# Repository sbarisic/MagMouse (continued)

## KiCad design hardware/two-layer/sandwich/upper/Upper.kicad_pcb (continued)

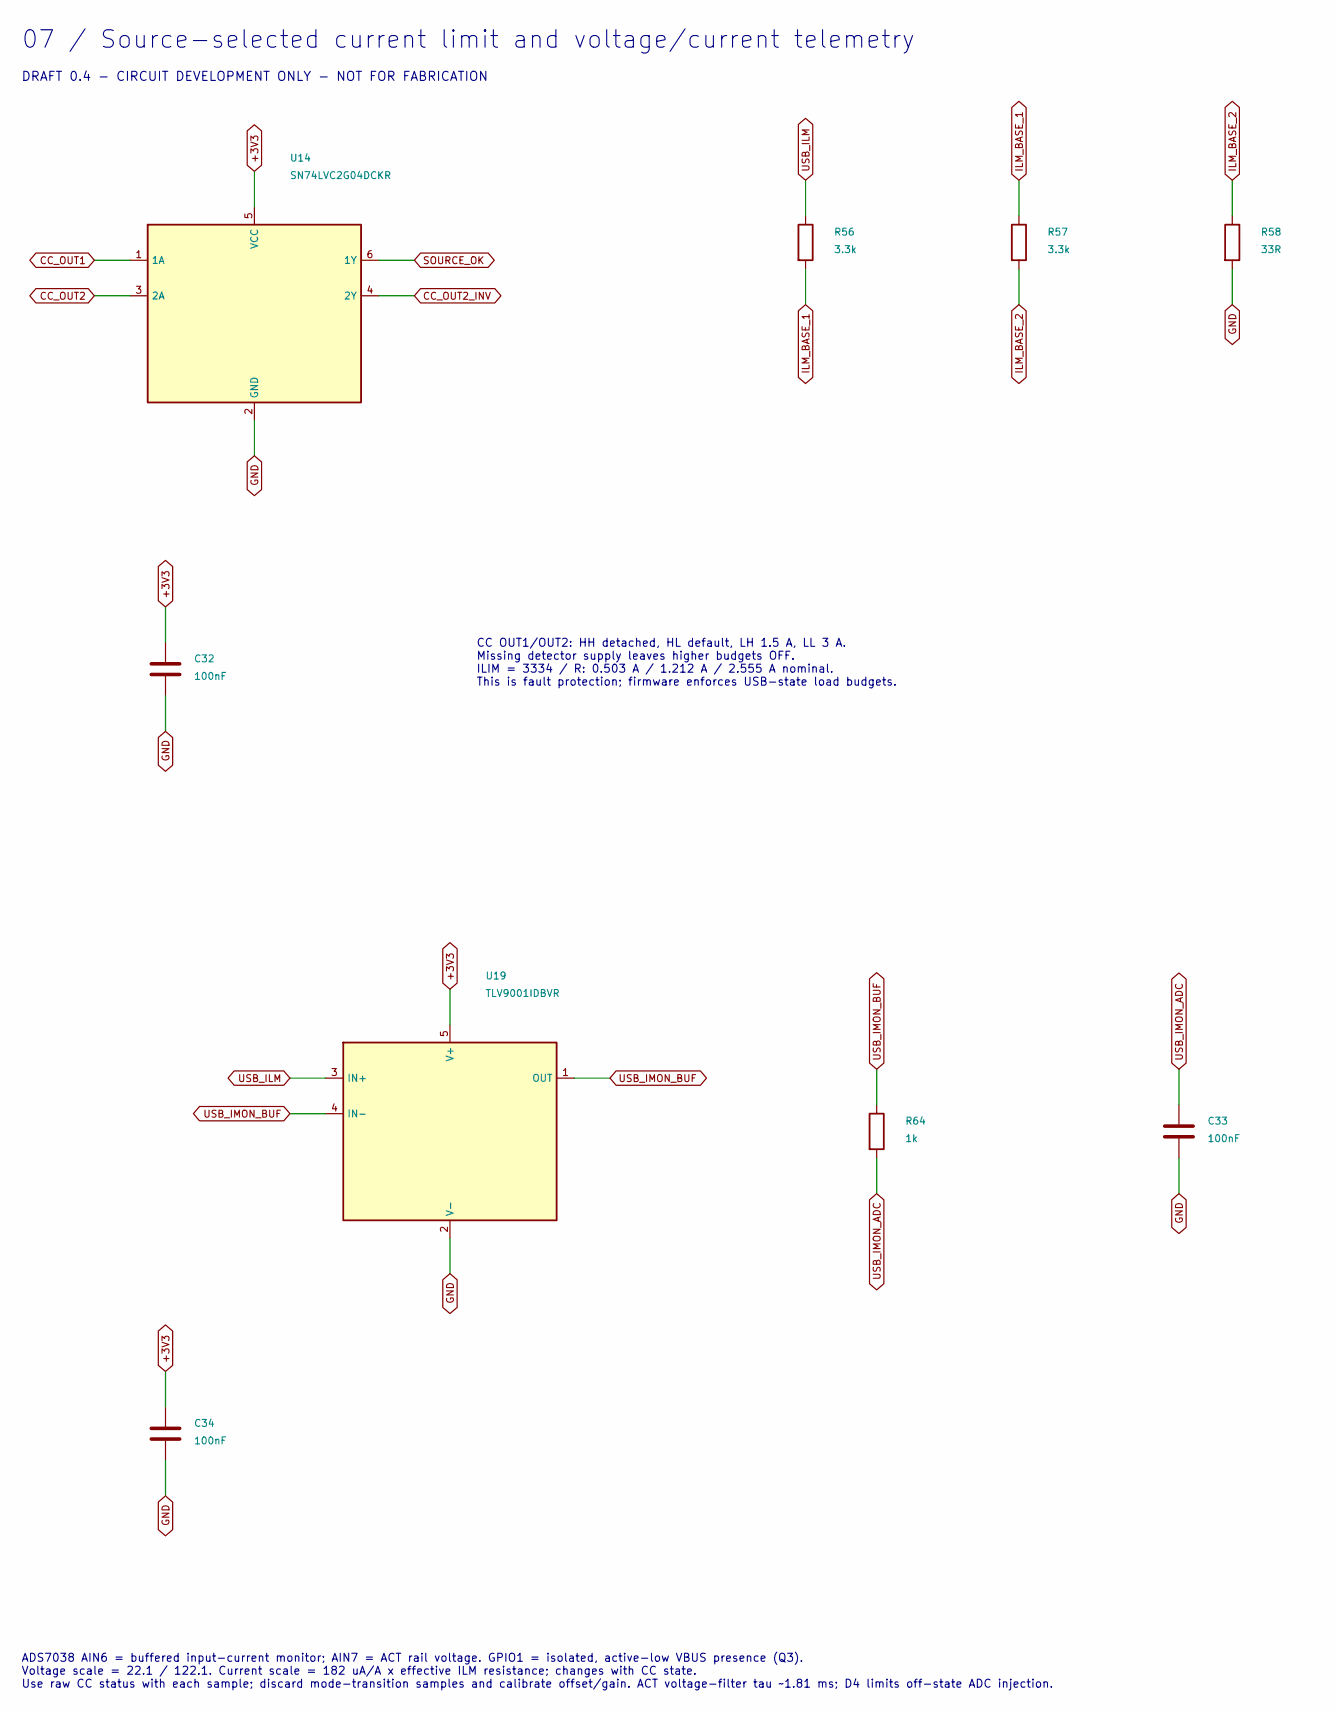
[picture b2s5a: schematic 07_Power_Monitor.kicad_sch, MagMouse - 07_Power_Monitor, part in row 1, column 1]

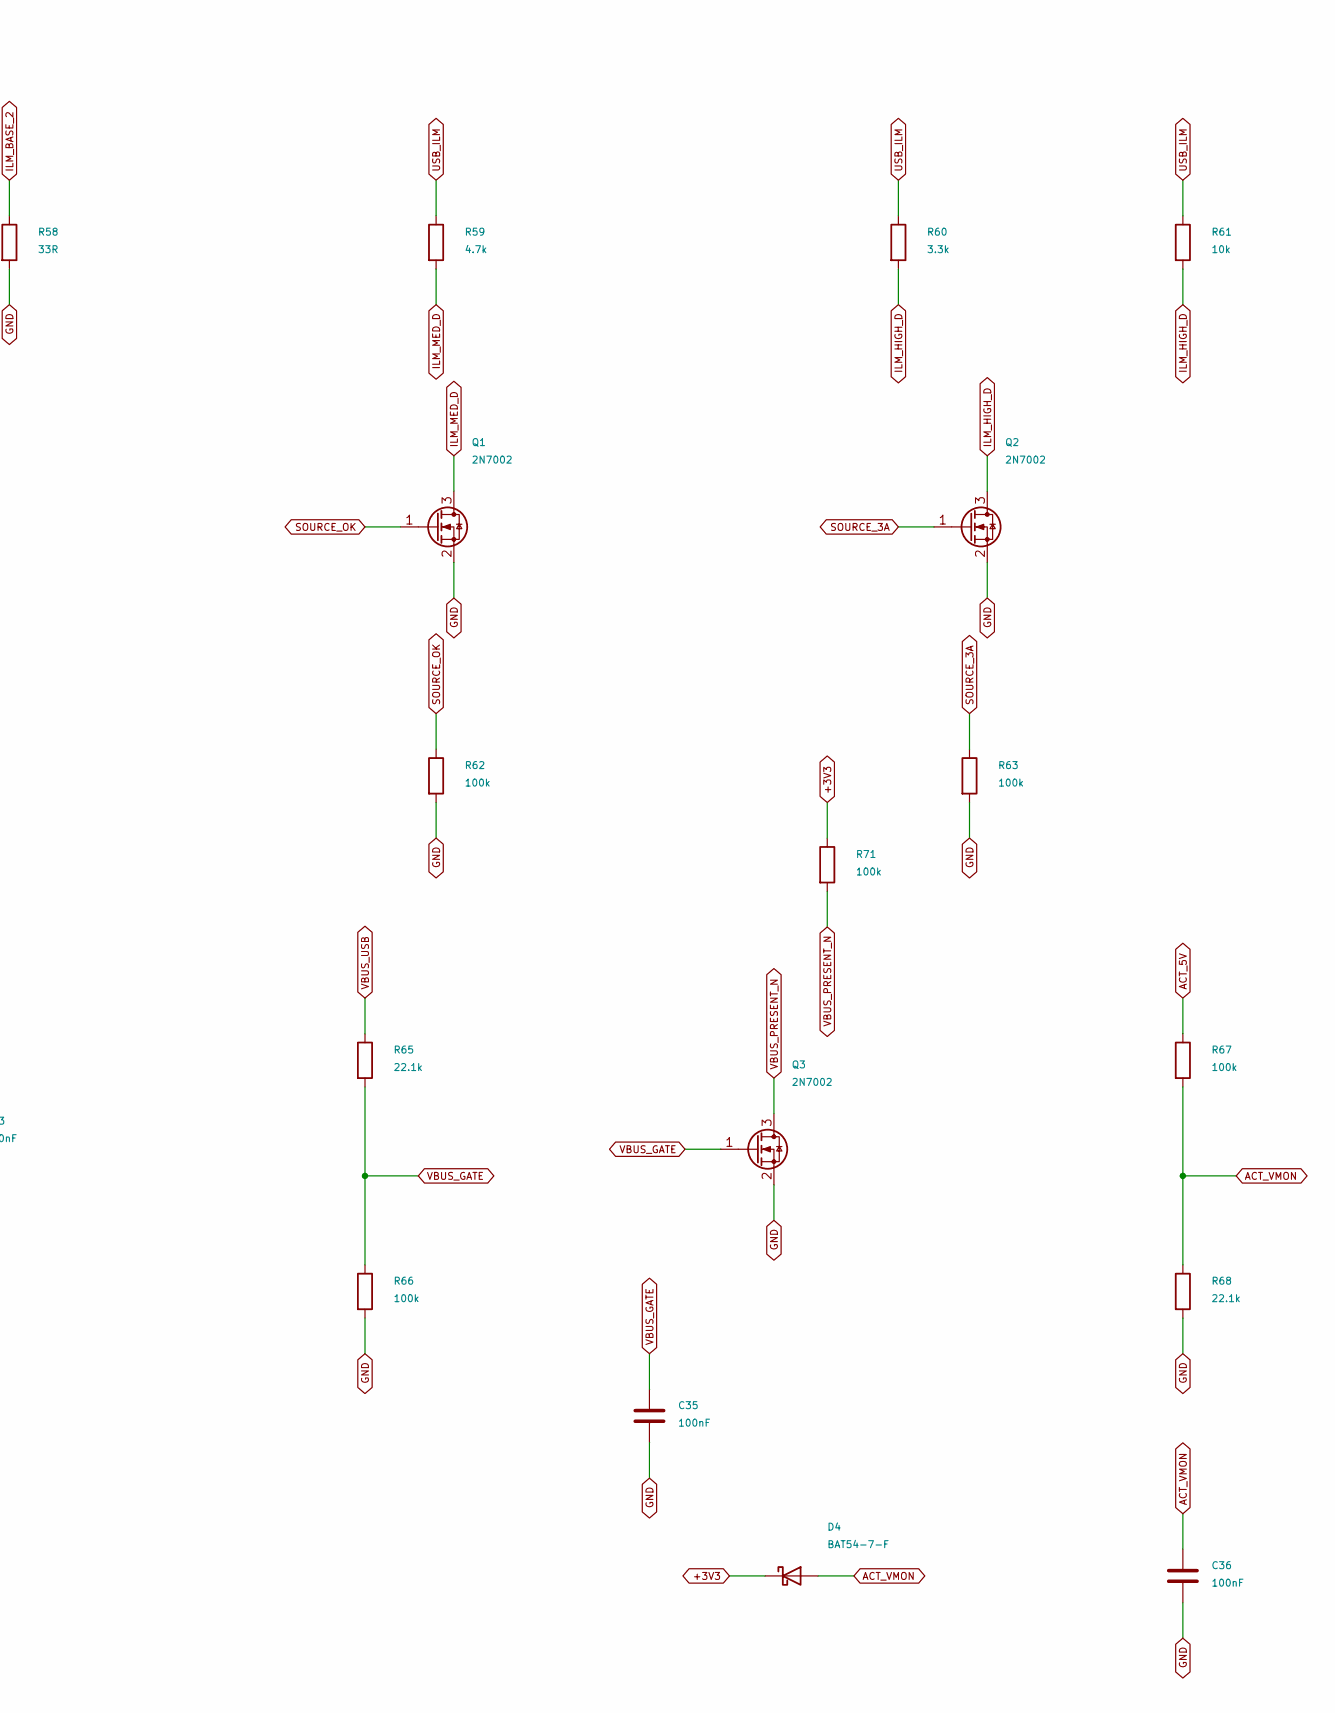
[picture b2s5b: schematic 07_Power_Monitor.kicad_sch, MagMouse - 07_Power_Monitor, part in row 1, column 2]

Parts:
C32, C33, C34, C35, C36: 100nF; C_1206_3216Metric; Rating 50 V, X7R, 10%; MPN CC1206KRX7R9BB104
D4: BAT54-7-F; SOT-23; MPN BAT54-7-F; LCSC C106920
Q1, Q2, Q3: 2N7002; SOT-23; MPN 2N7002; LCSC C8545
R56, R57, R60: 3.3k; R_1206_3216Metric; Rating 0.25 W, 1%; MPN RC1206FR-073K3L
R58: 33R; R_1206_3216Metric; Rating 0.25 W, 1%; MPN RC1206FR-0733RL
R59: 4.7k; R_1206_3216Metric; Rating 0.25 W, 1%; MPN RC1206FR-074K7L
R61: 10k; R_1206_3216Metric; Rating 0.25 W, 1%; MPN RC1206FR-0710KL
R62, R63, R66, R67, R71: 100k; R_1206_3216Metric; Rating 0.25 W, 1%; MPN RC1206FR-07100KL
R64: 1k; R_1206_3216Metric; Rating 0.25 W, 1%; MPN RC1206FR-071KL
R65, R68: 22.1k; R_1206_3216Metric; Rating 0.25 W, 1%; MPN RC1206FR-0722K1L
U14: SN74LVC2G04DCKR; SOT-363_SC-70-6; MPN SN74LVC2G04DCKR; LCSC C105251
U19: TLV9001IDBVR; SOT-23-5; MPN TLV9001IDBVR; LCSC C398363

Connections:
+3V3: C32.1, C34.1, D4.3 (K), R71.1, U14.5 (VCC), U19.5 (V+); also elsewhere on the board
ACT_5V: R67.1; also elsewhere on the board
ACT_VMON: C36.1, D4.1 (A), R67.2, R68.1; also elsewhere on the board
CC_OUT1: U14.1 (1A); also elsewhere on the board
CC_OUT2: U14.3 (2A); also elsewhere on the board
CC_OUT2_INV: U14.4 (2Y); also elsewhere on the board
GND: C32.2, C33.2, C34.2, C35.2, C36.2, Q1.2 (S), Q2.2 (S), Q3.2 (S), R58.2, R62.2, R63.2, R66.2, R68.2, U14.2 (GND), U19.2 (V-); also elsewhere on the board
ILM_BASE_1: R56.2, R57.1
ILM_BASE_2: R57.2, R58.1
ILM_HIGH_D: Q2.3 (D), R60.2, R61.2
ILM_MED_D: Q1.3 (D), R59.2
SOURCE_3A: Q2.1 (G), R63.1; also elsewhere on the board
SOURCE_OK: Q1.1 (G), R62.1, U14.6 (1Y); also elsewhere on the board
USB_ILM: R56.1, R59.1, R60.1, R61.1, U19.3 (IN+); also elsewhere on the board
USB_IMON_ADC: C33.1, R64.2; also elsewhere on the board
USB_IMON_BUF: R64.1, U19.1 (OUT), U19.4 (IN-)
VBUS_GATE: C35.1, Q3.1 (G), R65.2, R66.1
VBUS_PRESENT_N: Q3.3 (D), R71.2; also elsewhere on the board
VBUS_USB: R65.1; also elsewhere on the board

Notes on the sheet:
07 / Source-selected current limit and voltage/current telemetry
DRAFT 0.4 - CIRCUIT DEVELOPMENT ONLY - NOT FOR FABRICATION
CC OUT1/OUT2: HH detached, HL default, LH 1.5 A, LL 3 A. Missing detector supply leaves higher budgets OFF. ILIM = 3334 / R: 0.503 A / 1.212 A / 2.555 A nominal. This is fault protection; firmware enforces USB-state load budgets.
ADS7038 AIN6 = buffered input-current monitor; AIN7 = ACT rail voltage. GPIO1 = isolated, active-low VBUS presence (Q3). Voltage scale = 22.1 / 122.1. Current scale = 182 uA/A x effective ILM resistance; changes with CC state. Use raw CC status with each sample; discard mode-transition samples and 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

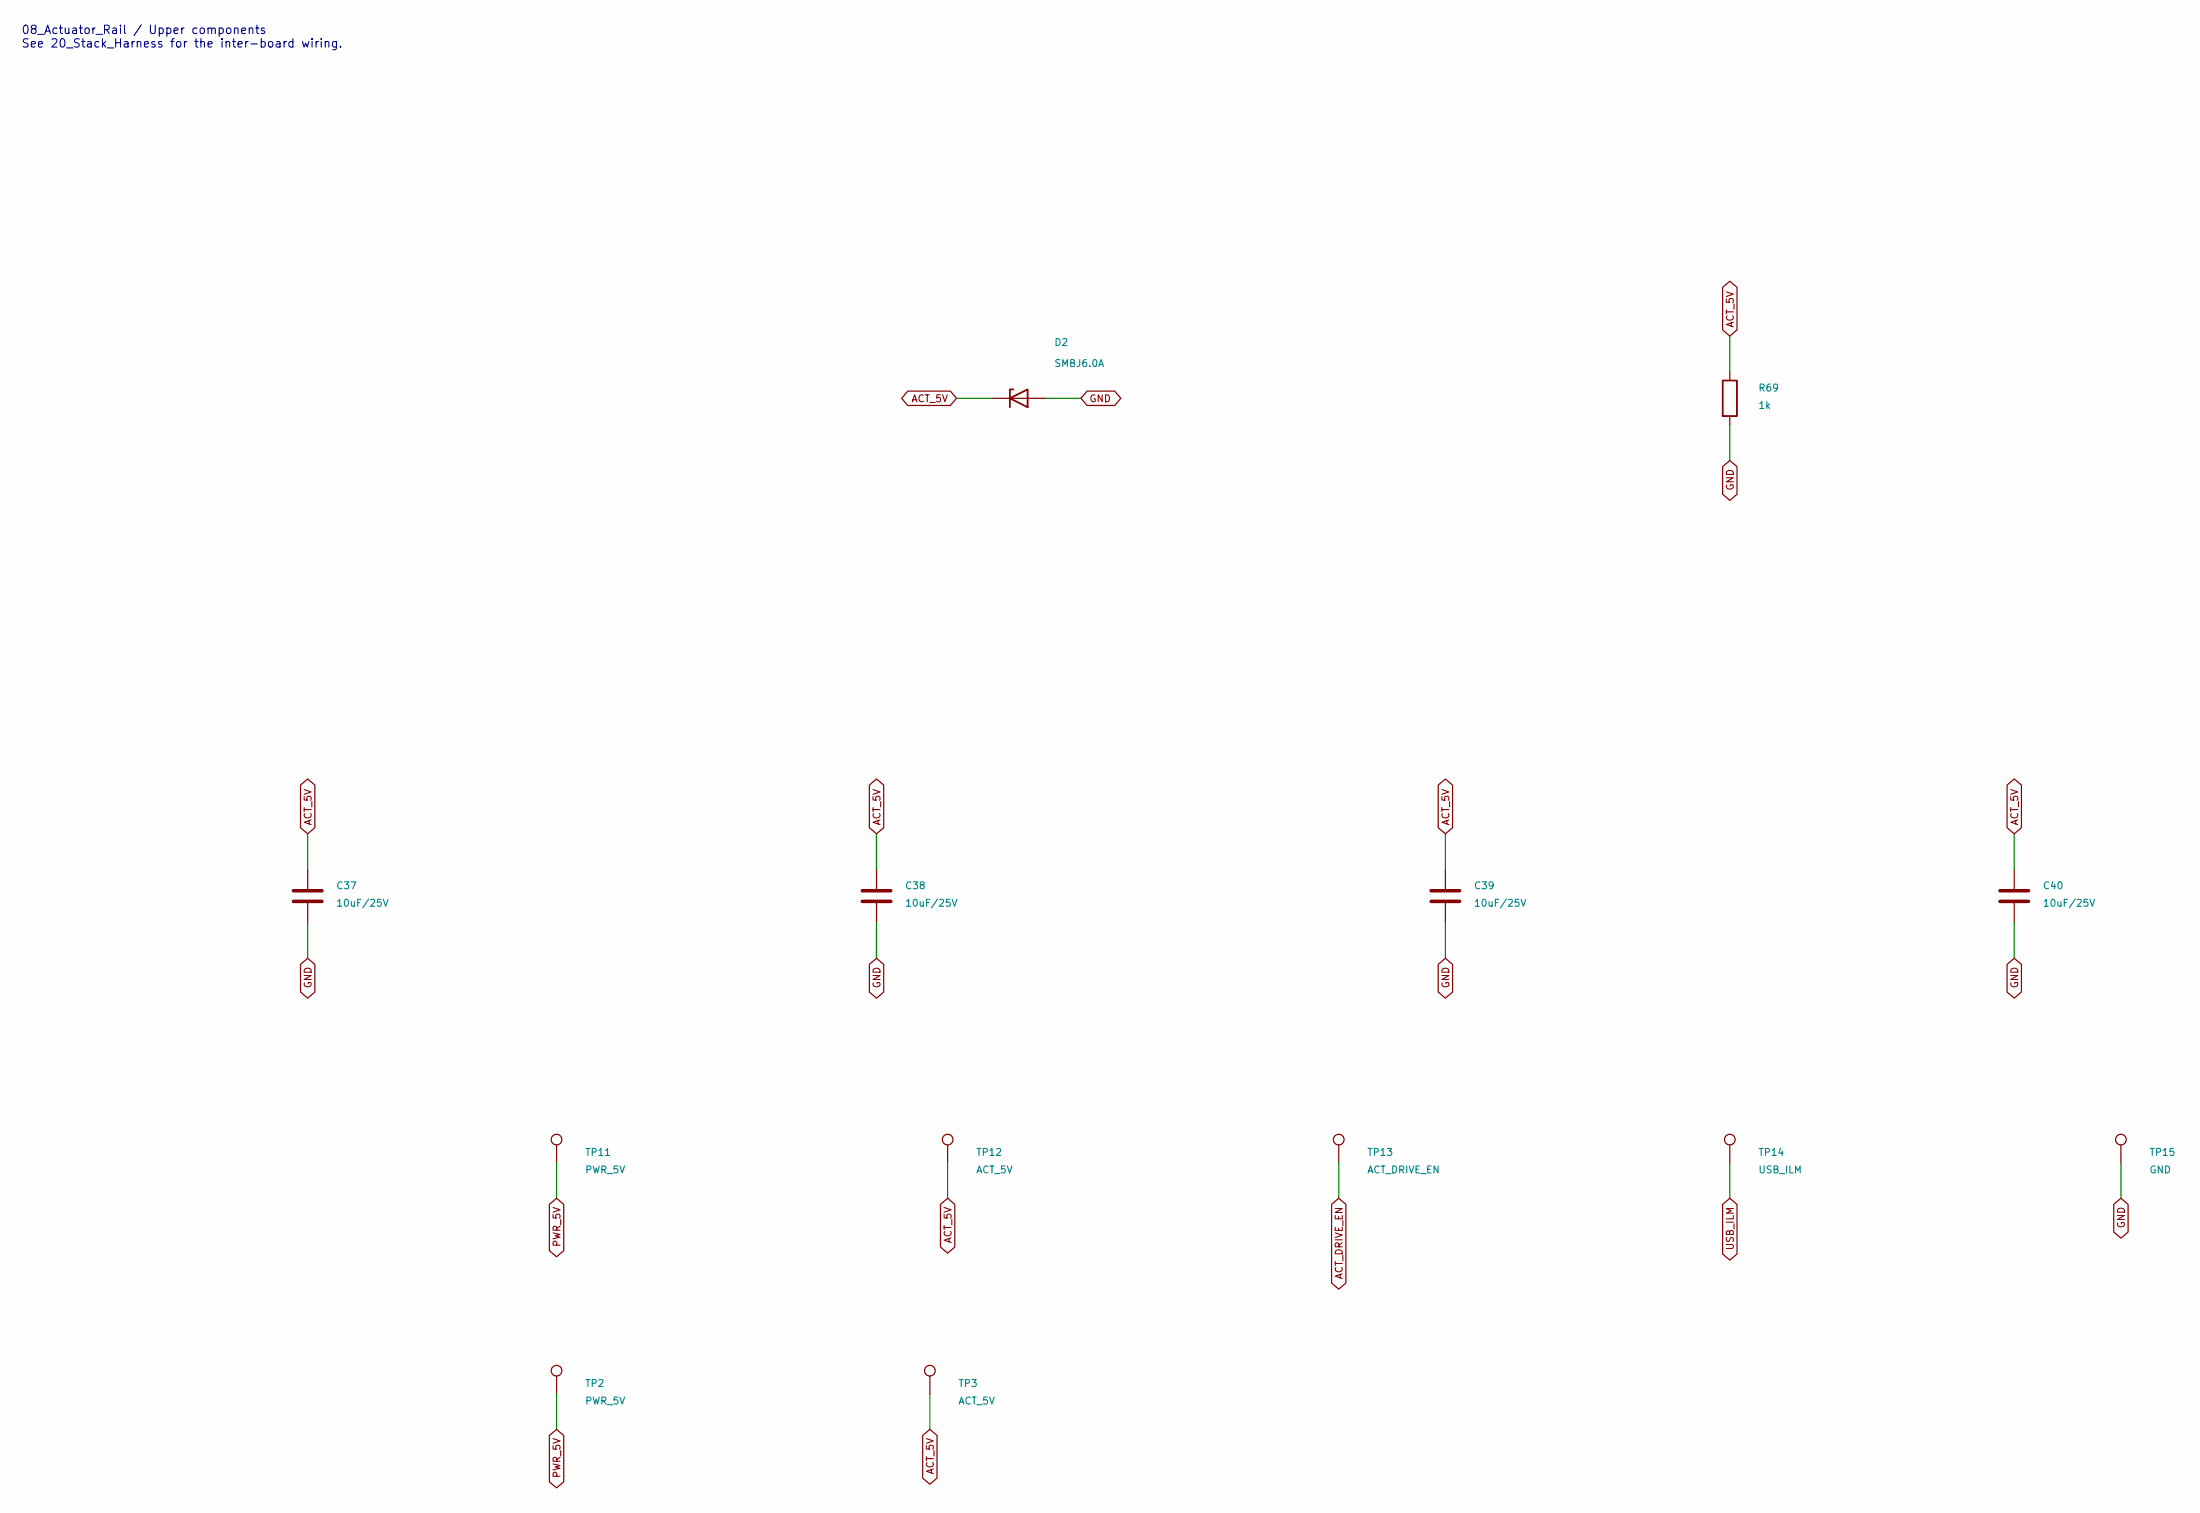
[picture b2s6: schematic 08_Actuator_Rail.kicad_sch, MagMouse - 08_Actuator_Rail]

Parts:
C37, C38, C39, C40: 10uF/25V; C_1206_3216Metric; Rating 25 V, X5R, 10%; MPN CL31A106KAHNNNE
D2: SMBJ6.0A; D_SMB; MPN SMBJ6.0A; LCSC C83270
R69: 1k; R_1206_3216Metric; Rating 0.25 W, 1%; MPN RC1206FR-071KL
TP2, TP11: PWR_5V; TestPoint_Pad_D1.0mm
TP3, TP12: ACT_5V; TestPoint_Pad_D1.0mm
TP13: ACT_DRIVE_EN; TestPoint_Pad_D1.0mm
TP14: USB_ILM; TestPoint_Pad_D1.0mm
TP15: GND; TestPoint_Pad_D1.0mm

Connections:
ACT_5V: C37.1, C38.1, C39.1, C40.1, D2.1 (K), R69.1, TP3.1, TP12.1; also elsewhere on the board
ACT_DRIVE_EN: TP13.1; also elsewhere on the board
GND: C37.2, C38.2, C39.2, C40.2, D2.2 (A), R69.2, TP15.1; also elsewhere on the board
PWR_5V: TP2.1, TP11.1; also elsewhere on the board
USB_ILM: TP14.1; also elsewhere on the board

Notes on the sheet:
08_Actuator_Rail / Upper components See 20_Stack_Harness for the inter-board wiring.

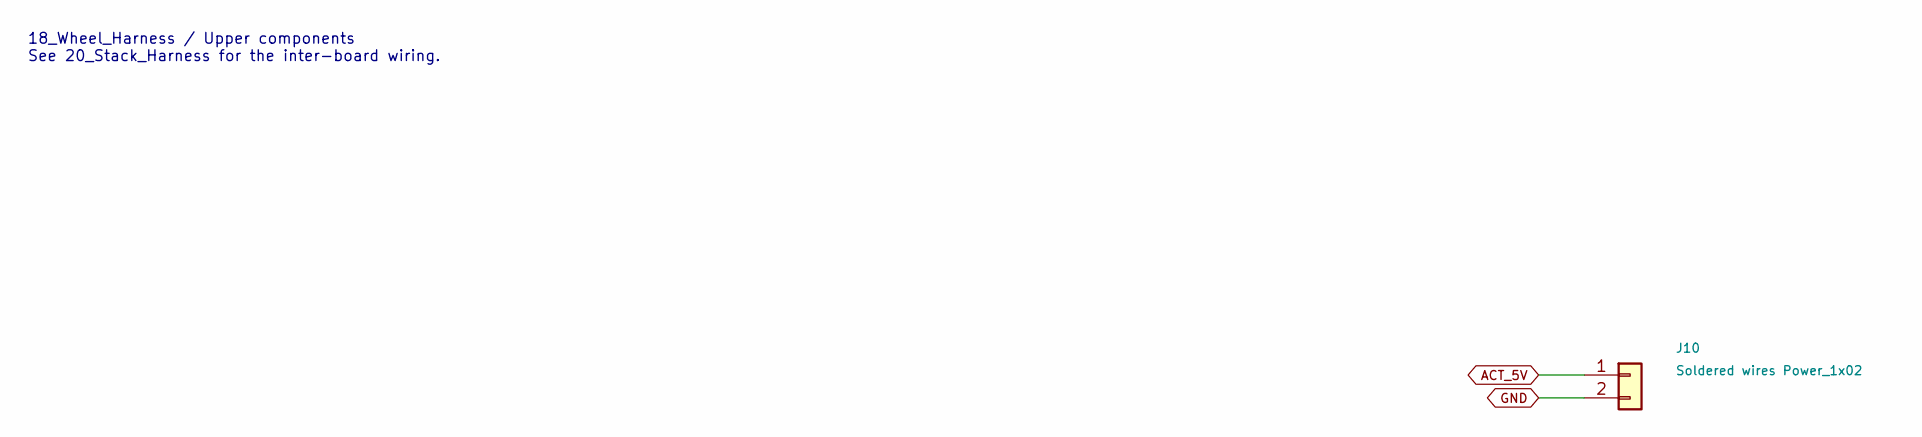
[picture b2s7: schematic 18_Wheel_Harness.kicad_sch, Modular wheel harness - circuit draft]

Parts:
J10: Soldered wires Power_1x02; Wire_Power_1x02_P2.54mm

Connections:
ACT_5V: J10.1; also elsewhere on the board
GND: J10.2; also elsewhere on the board

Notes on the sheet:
18_Wheel_Harness / Upper components See 20_Stack_Harness for the inter-board wiring.

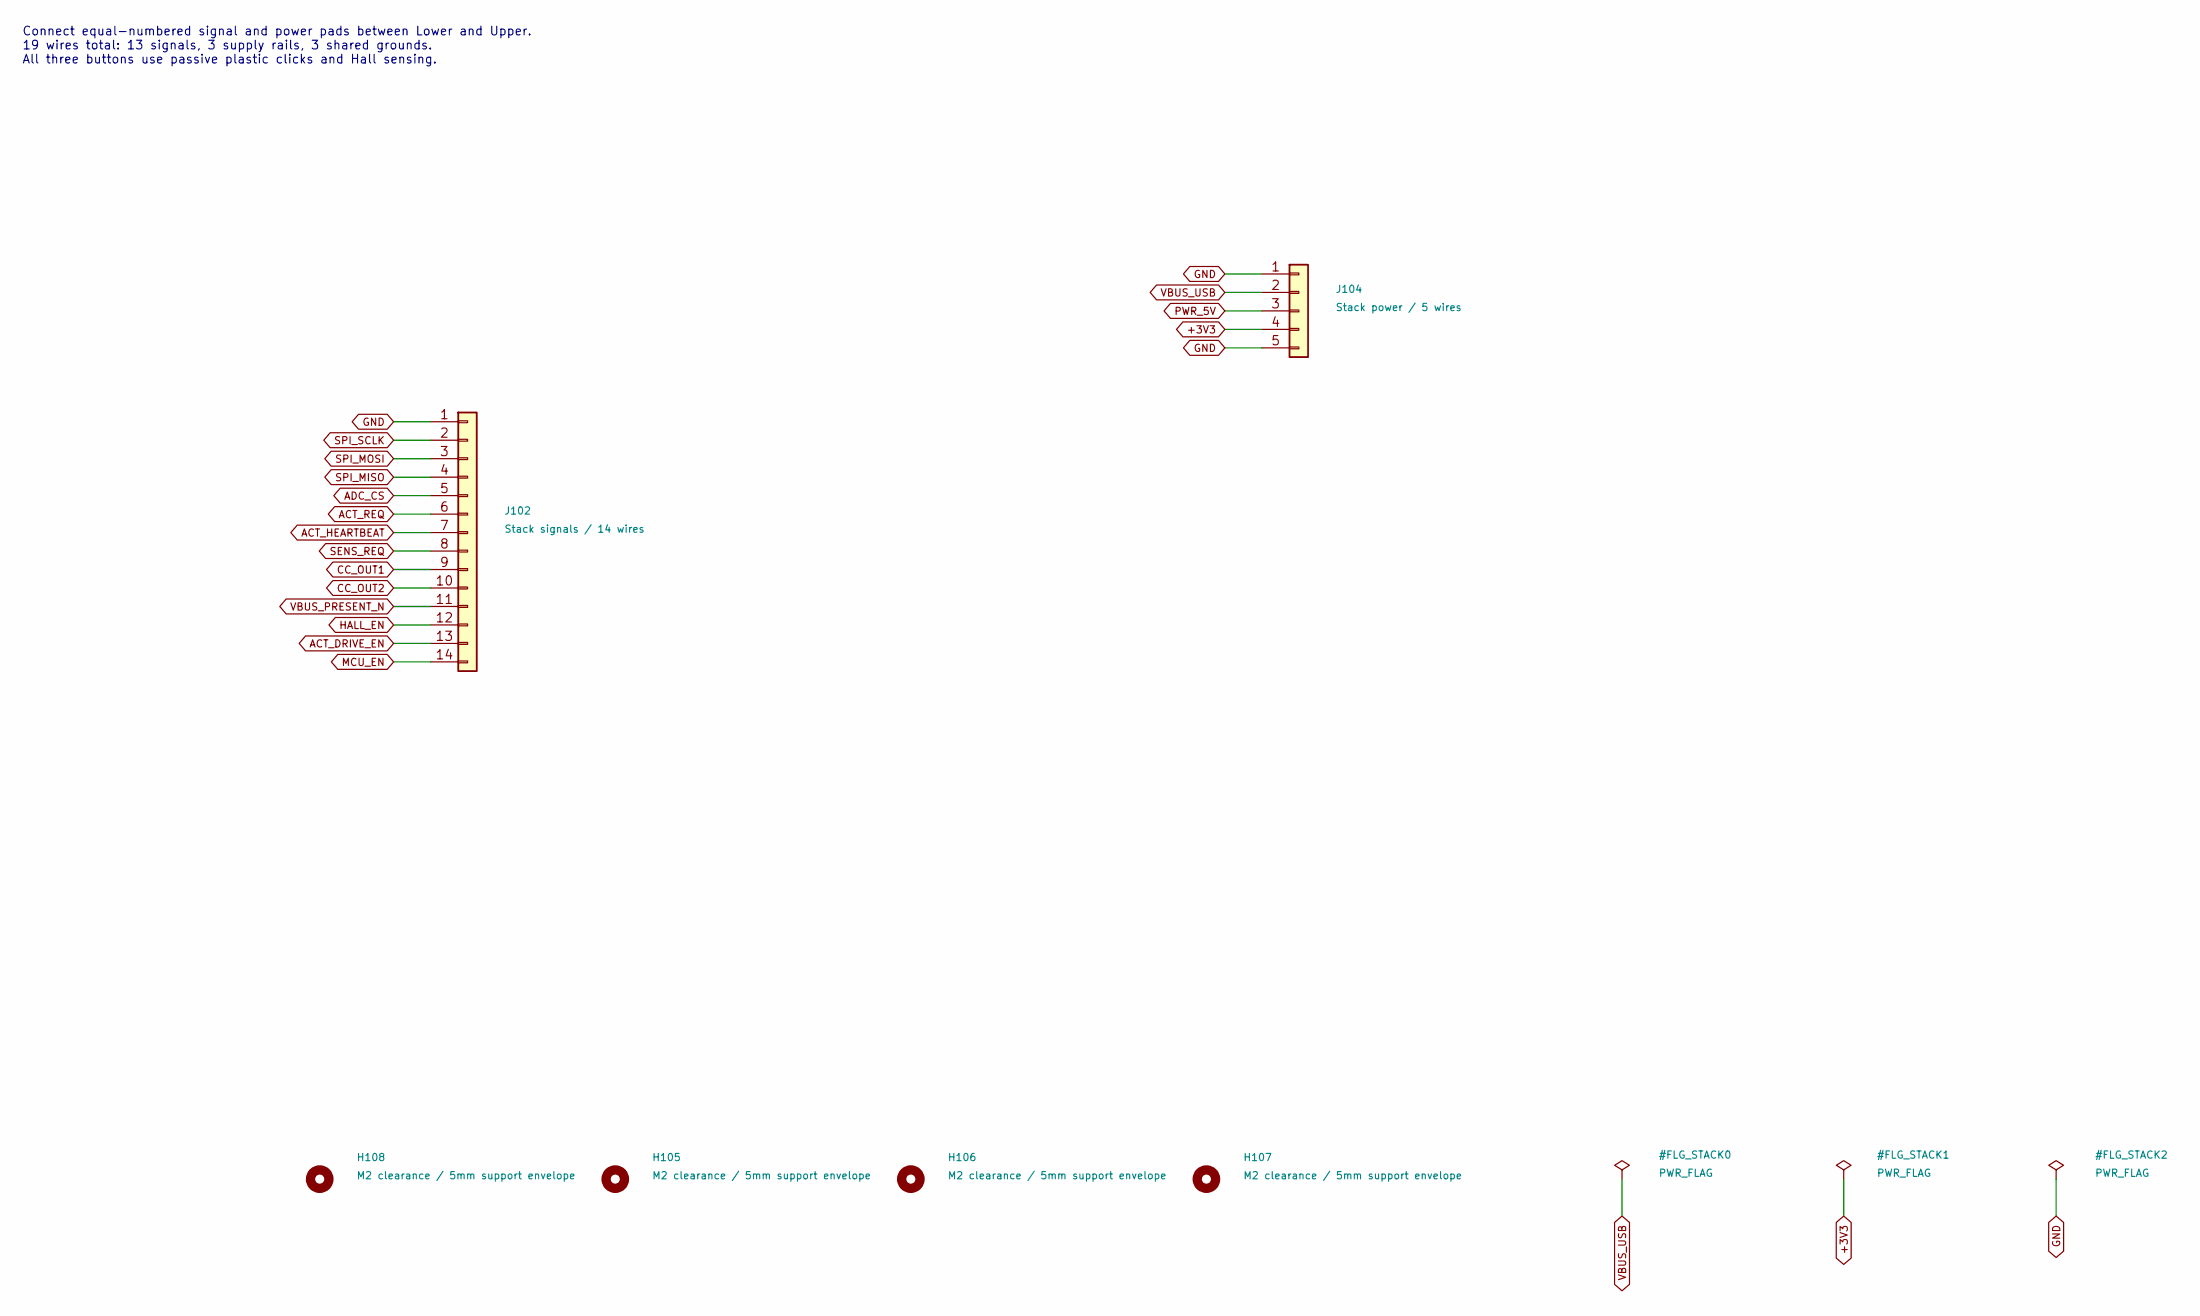
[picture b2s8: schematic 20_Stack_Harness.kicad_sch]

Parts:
H105, H106, H107, H108: M2 clearance / 5mm support envelope; MountingHole_2.2mm_M2_5mm_Envelope
J102: Stack signals / 14 wires; Wire_Stack_Signal_14
J104: Stack power / 5 wires; Wire_Stack_Power_5

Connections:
+3V3: J104.4; also elsewhere on the board
ACT_DRIVE_EN: J102.13; also elsewhere on the board
ACT_HEARTBEAT: J102.7; also elsewhere on the board
ACT_REQ: J102.6; also elsewhere on the board
ADC_CS: J102.5; also elsewhere on the board
CC_OUT1: J102.9; also elsewhere on the board
CC_OUT2: J102.10; also elsewhere on the board
GND: J102.1, J104.1, J104.5; also elsewhere on the board
HALL_EN: J102.12; also elsewhere on the board
MCU_EN: J102.14; also elsewhere on the board
PWR_5V: J104.3; also elsewhere on the board
SENS_REQ: J102.8; also elsewhere on the board
SPI_MISO: J102.4; also elsewhere on the board
SPI_MOSI: J102.3; also elsewhere on the board
SPI_SCLK: J102.2; also elsewhere on the board
VBUS_PRESENT_N: J102.11; also elsewhere on the board
VBUS_USB: J104.2; also elsewhere on the board

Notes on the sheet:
Connect equal-numbered signal and power pads between Lower and Upper. 19 wires total: 13 signals, 3 supply rails, 3 shared grounds. All three buttons use passive plastic clicks and Hall sensing.

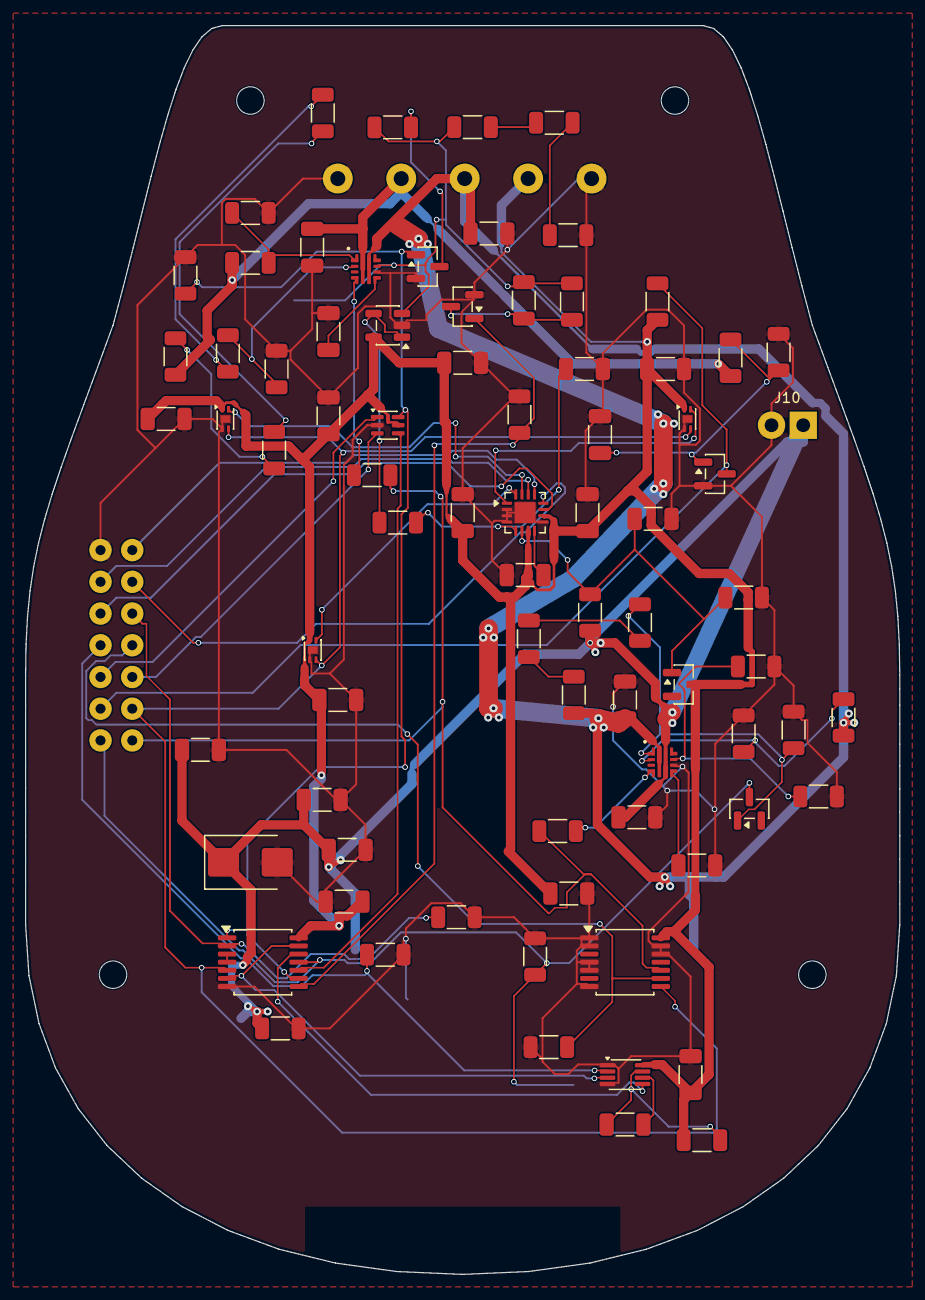
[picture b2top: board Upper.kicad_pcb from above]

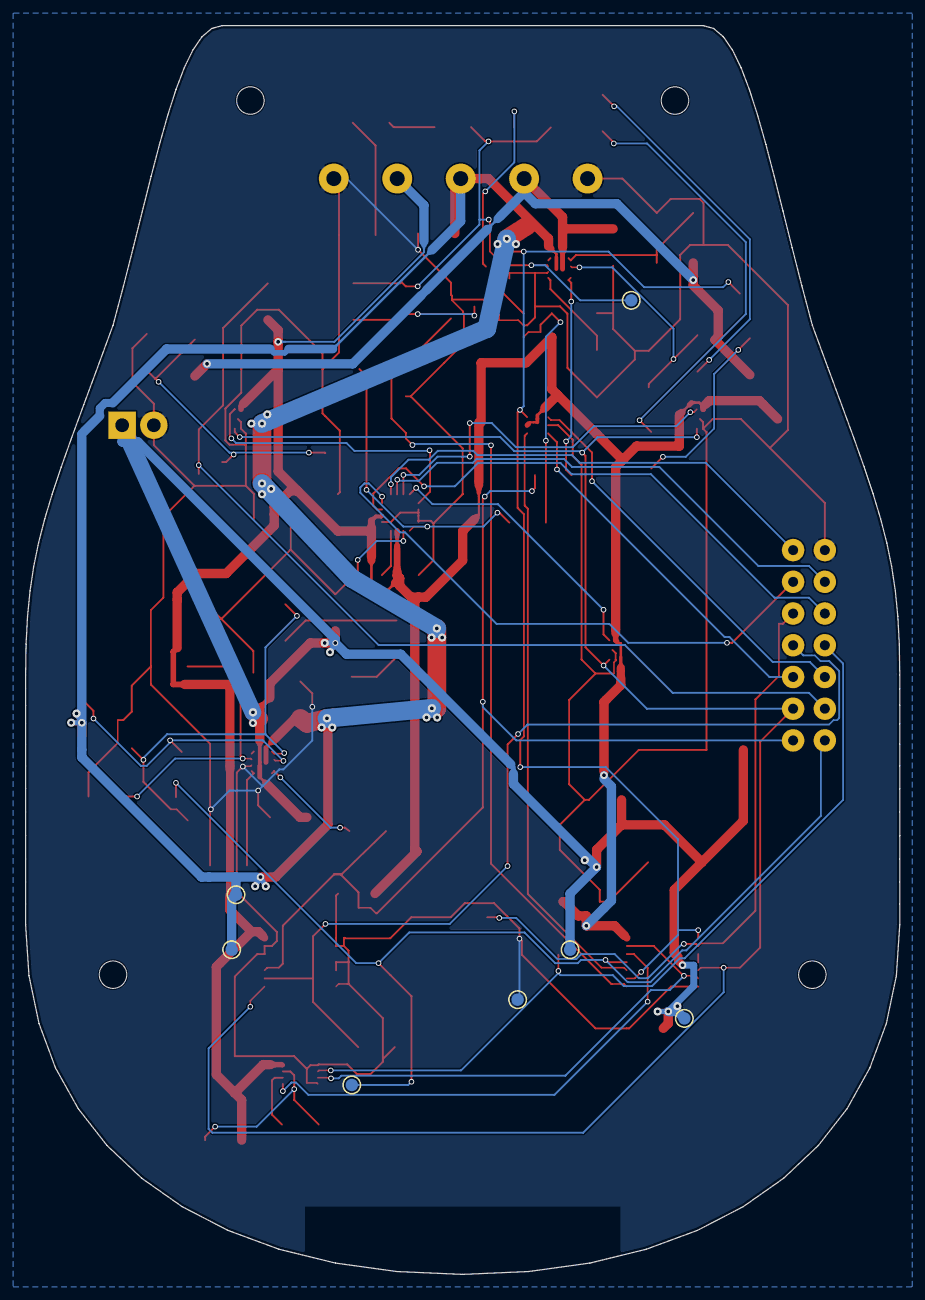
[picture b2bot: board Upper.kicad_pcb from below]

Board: 2 copper layers, 70.0 x 100.0 mm, 92 parts (7 on the bottom side), 53 nets.

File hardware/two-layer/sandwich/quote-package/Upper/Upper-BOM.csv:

Comment,Designator,Footprint,LCSC Part #,Manufacturer,MPN,Quantity
100nF,"C16,C17,C18,C28,C29,C31,C32,C33,C34,C35,C36",C_1206_3216Metric,,YAGEO,CC1206KRX7R9BB104,11
1uF/50V,"C19,C20,C21,C24,C27,C89",C_1206_3216Metric,,Samsung Electro-Mechanics,CL31B105KBHNNNE,6
10nF,"C25,C26",C_1206_3216Metric,,YAGEO,CC1206KRX7R9BB103,2
10uF/25V,"C37,C38,C39,C40,C88",C_1206_3216Metric,,Samsung Electro-Mechanics,CL31A106KAHNNNE,5
SMBJ6.0A,D2,D_SMB,C83270,Littelfuse,SMBJ6.0A,1
BAT54-7-F,"D3,D4",SOT-23,C106920,Diodes Incorporated,BAT54-7-F,2
2N7002,"Q1,Q2,Q3",SOT-23,C8545,Jiangsu Changjing Electronics Technology,2N7002,3
22.1k,"R29,R41,R65,R68",R_1206_3216Metric,,YAGEO,RC1206FR-0722K1L,4
10k,"R30,R46,R47,R48,R49,R61,R70",R_1206_3216Metric,,YAGEO,RC1206FR-0710KL,7
100k,"R31,R32,R33,R34,R35,R36,R37,R38,R39,R40,R62,R63,R66,R67,R71",R_1206_3216Metric,,YAGEO,RC1206FR-07100KL,15
3.3k,"R42,R43,R56,R57,R60",R_1206_3216Metric,,YAGEO,RC1206FR-073K3L,5
1k,"R44,R45,R64,R69",R_1206_3216Metric,,YAGEO,RC1206FR-071KL,4
33R,R58,R_1206_3216Metric,,YAGEO,RC1206FR-0733RL,1
4.7k,R59,R_1206_3216Metric,,YAGEO,RC1206FR-074K7L,1
ADS7038IRTER,U10,WQFN-16-1EP_3x3mm_P0.5mm_EP1.68x1.68mm,C2871580,Texas Instruments,ADS7038IRTER,1
TPS259470LRPWR,"U12,U13",Texas_RPW0010A,C3662793,Texas Instruments,TPS259470LRPWR,2
SN74LVC2G04DCKR,U14,SOT-363_SC-70-6,C105251,Texas Instruments,SN74LVC2G04DCKR,1
SN74LVC1G123DCUR,U15,VSSOP-8_2.3x2mm_P0.5mm,C352969,Texas Instruments,SN74LVC1G123DCUR,1
SN74LVC08APWR,"U16,U18",TSSOP-14_4.4x5mm_P0.65mm,C465737,Texas Instruments,SN74LVC08APWR,2
TLV9001IDBVR,U19,SOT-23-5,C398363,Texas Instruments,TLV9001IDBVR,1
TMAG5253BA2IQDMRR,"U7,U8,U9",Texas_X2SON-4-1EP_1.1x1.4mm_P0.5mm_EP0.8x0.6mm,C35414983,Texas Instruments,TMAG5253BA2IQDMRR,3

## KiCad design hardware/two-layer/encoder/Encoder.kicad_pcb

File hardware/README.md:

# Electronics

The [active four-board design](two-layer/sandwich/README.md) uses two copper
layers on each board, passive plastic button clicks and Hall sensing.
Lower and Upper are 70 x 100 mm; Wheel is 70 x 67 mm; Encoder is 14 x 18 mm
with chamfered top corners. All four have independent schematics and routing.

- [Editable projects and reviews](two-layer/sandwich/README.md)
- [Manufacturing quote package](two-layer/sandwich/quote-package/README.md)
- [Combined panel](two-layer/sandwich/panel/Panel.kicad_pcb)
- [3D models](two-layer/sandwich/3d/README.md)
- [Shared libraries and helpers](common/README.md)
- [Historical brake simulation](simulation/brake/README.md)
- [Previous revisions in Git](../docs/history/README.md)

Mechanical integration, supplier acceptance, firmware and physical electronics
qualification remain open. The legacy BOM and circuit/layout notes outside the
active projects contain historical material; use the active schematics and
quote-package BOM for the current fitted components.

License: CERN-OHL-S-2.0; see [LICENSE](LICENSE).
Source location: <https://github.com/sbarisic/MagMouse>.

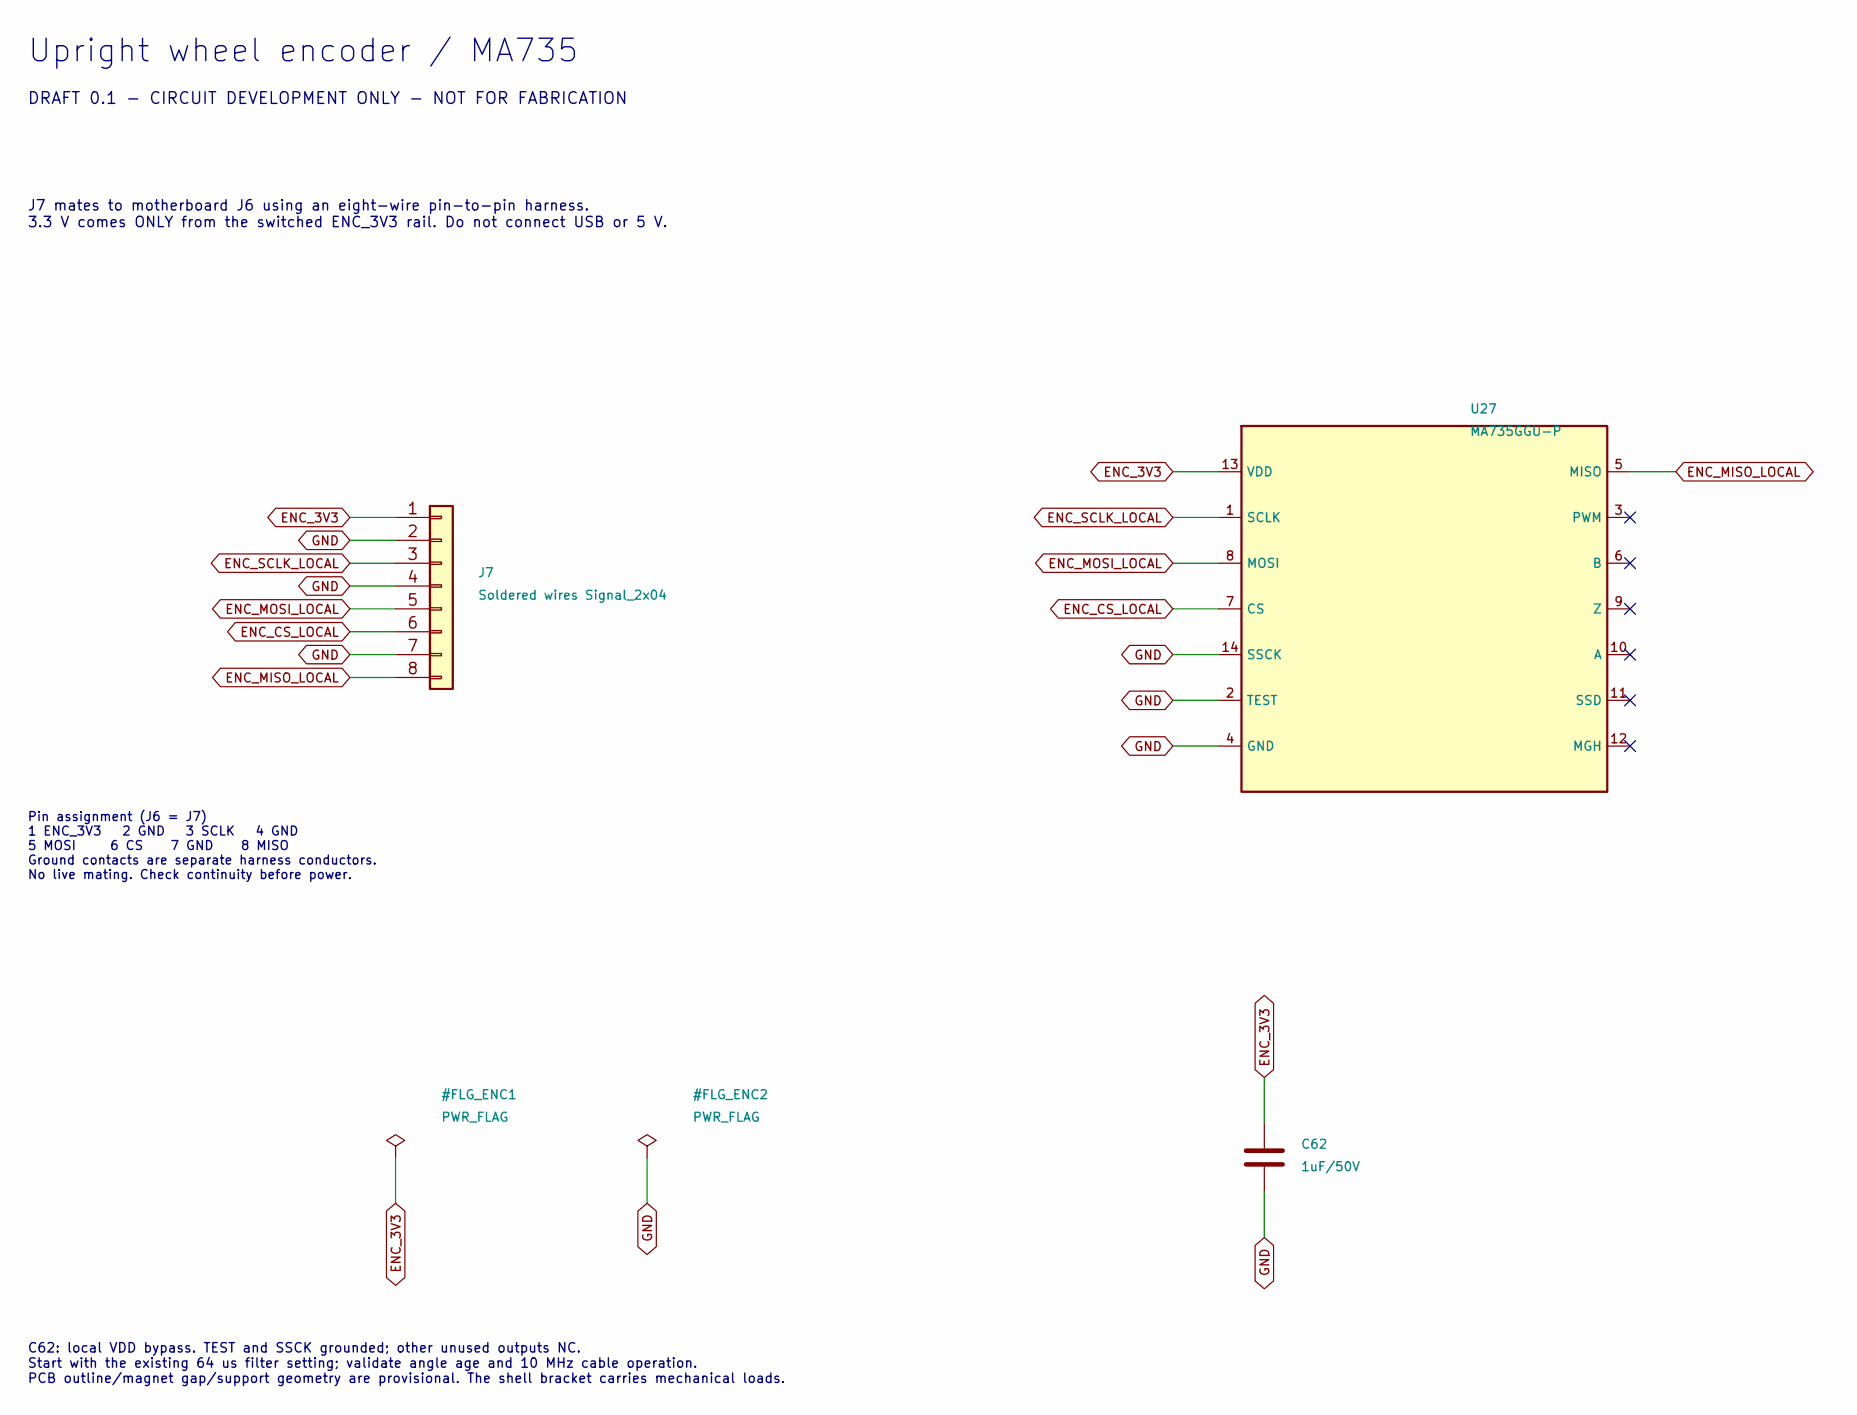
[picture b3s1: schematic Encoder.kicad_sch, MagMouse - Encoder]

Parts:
C62: 1uF/50V; C_1206_3216Metric; Rating 50 V, X7R, 10%; MPN CL31B105KBHNNNE
J7: Soldered wires Signal_2x04; Wire_Signal_2x04_P2.54mm
U27: MA735GGU-P; MPS_UTQFN14_2x2; MPN MA735GGU-P; LCSC C17233427

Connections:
ENC_3V3: C62.1, J7.1, U27.13 (VDD)
ENC_CS_LOCAL: J7.6, U27.7 (CS)
ENC_MISO_LOCAL: J7.8, U27.5 (MISO)
ENC_MOSI_LOCAL: J7.5, U27.8 (MOSI)
ENC_SCLK_LOCAL: J7.3, U27.1 (SCLK)
GND: C62.2, J7.2, J7.4, J7.7, U27.2 (TEST), U27.4 (GND), U27.14 (SSCK)

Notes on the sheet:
Upright wheel encoder / MA735
DRAFT 0.1 - CIRCUIT DEVELOPMENT ONLY - NOT FOR FABRICATION
J7 mates to motherboard J6 using an eight-wire pin-to-pin harness. 3.3 V comes ONLY from the switched ENC_3V3 rail. Do not connect USB or 5 V.
Pin assignment (J6 = J7) 1 ENC_3V3 2 GND 3 SCLK 4 GND 5 MOSI 6 CS 7 GND 8 MISO Ground contacts are separate harness conductors. No live mating. Check continuity before power.
C62: local VDD bypass. TEST and SSCK grounded; other unused outputs NC. Start with the existing 64 us filter setting; validate angle age and 10 MHz cable operation. PCB outline/magnet gap/support geometry are provisional. The shell bracket carries mechanical loads.

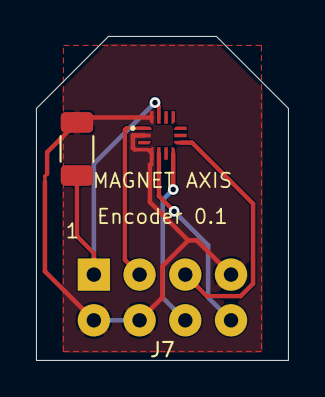
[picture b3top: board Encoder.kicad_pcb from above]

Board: 2 copper layers, 14.0 x 18.0 mm, 3 parts (0 on the bottom side), 6 nets.
